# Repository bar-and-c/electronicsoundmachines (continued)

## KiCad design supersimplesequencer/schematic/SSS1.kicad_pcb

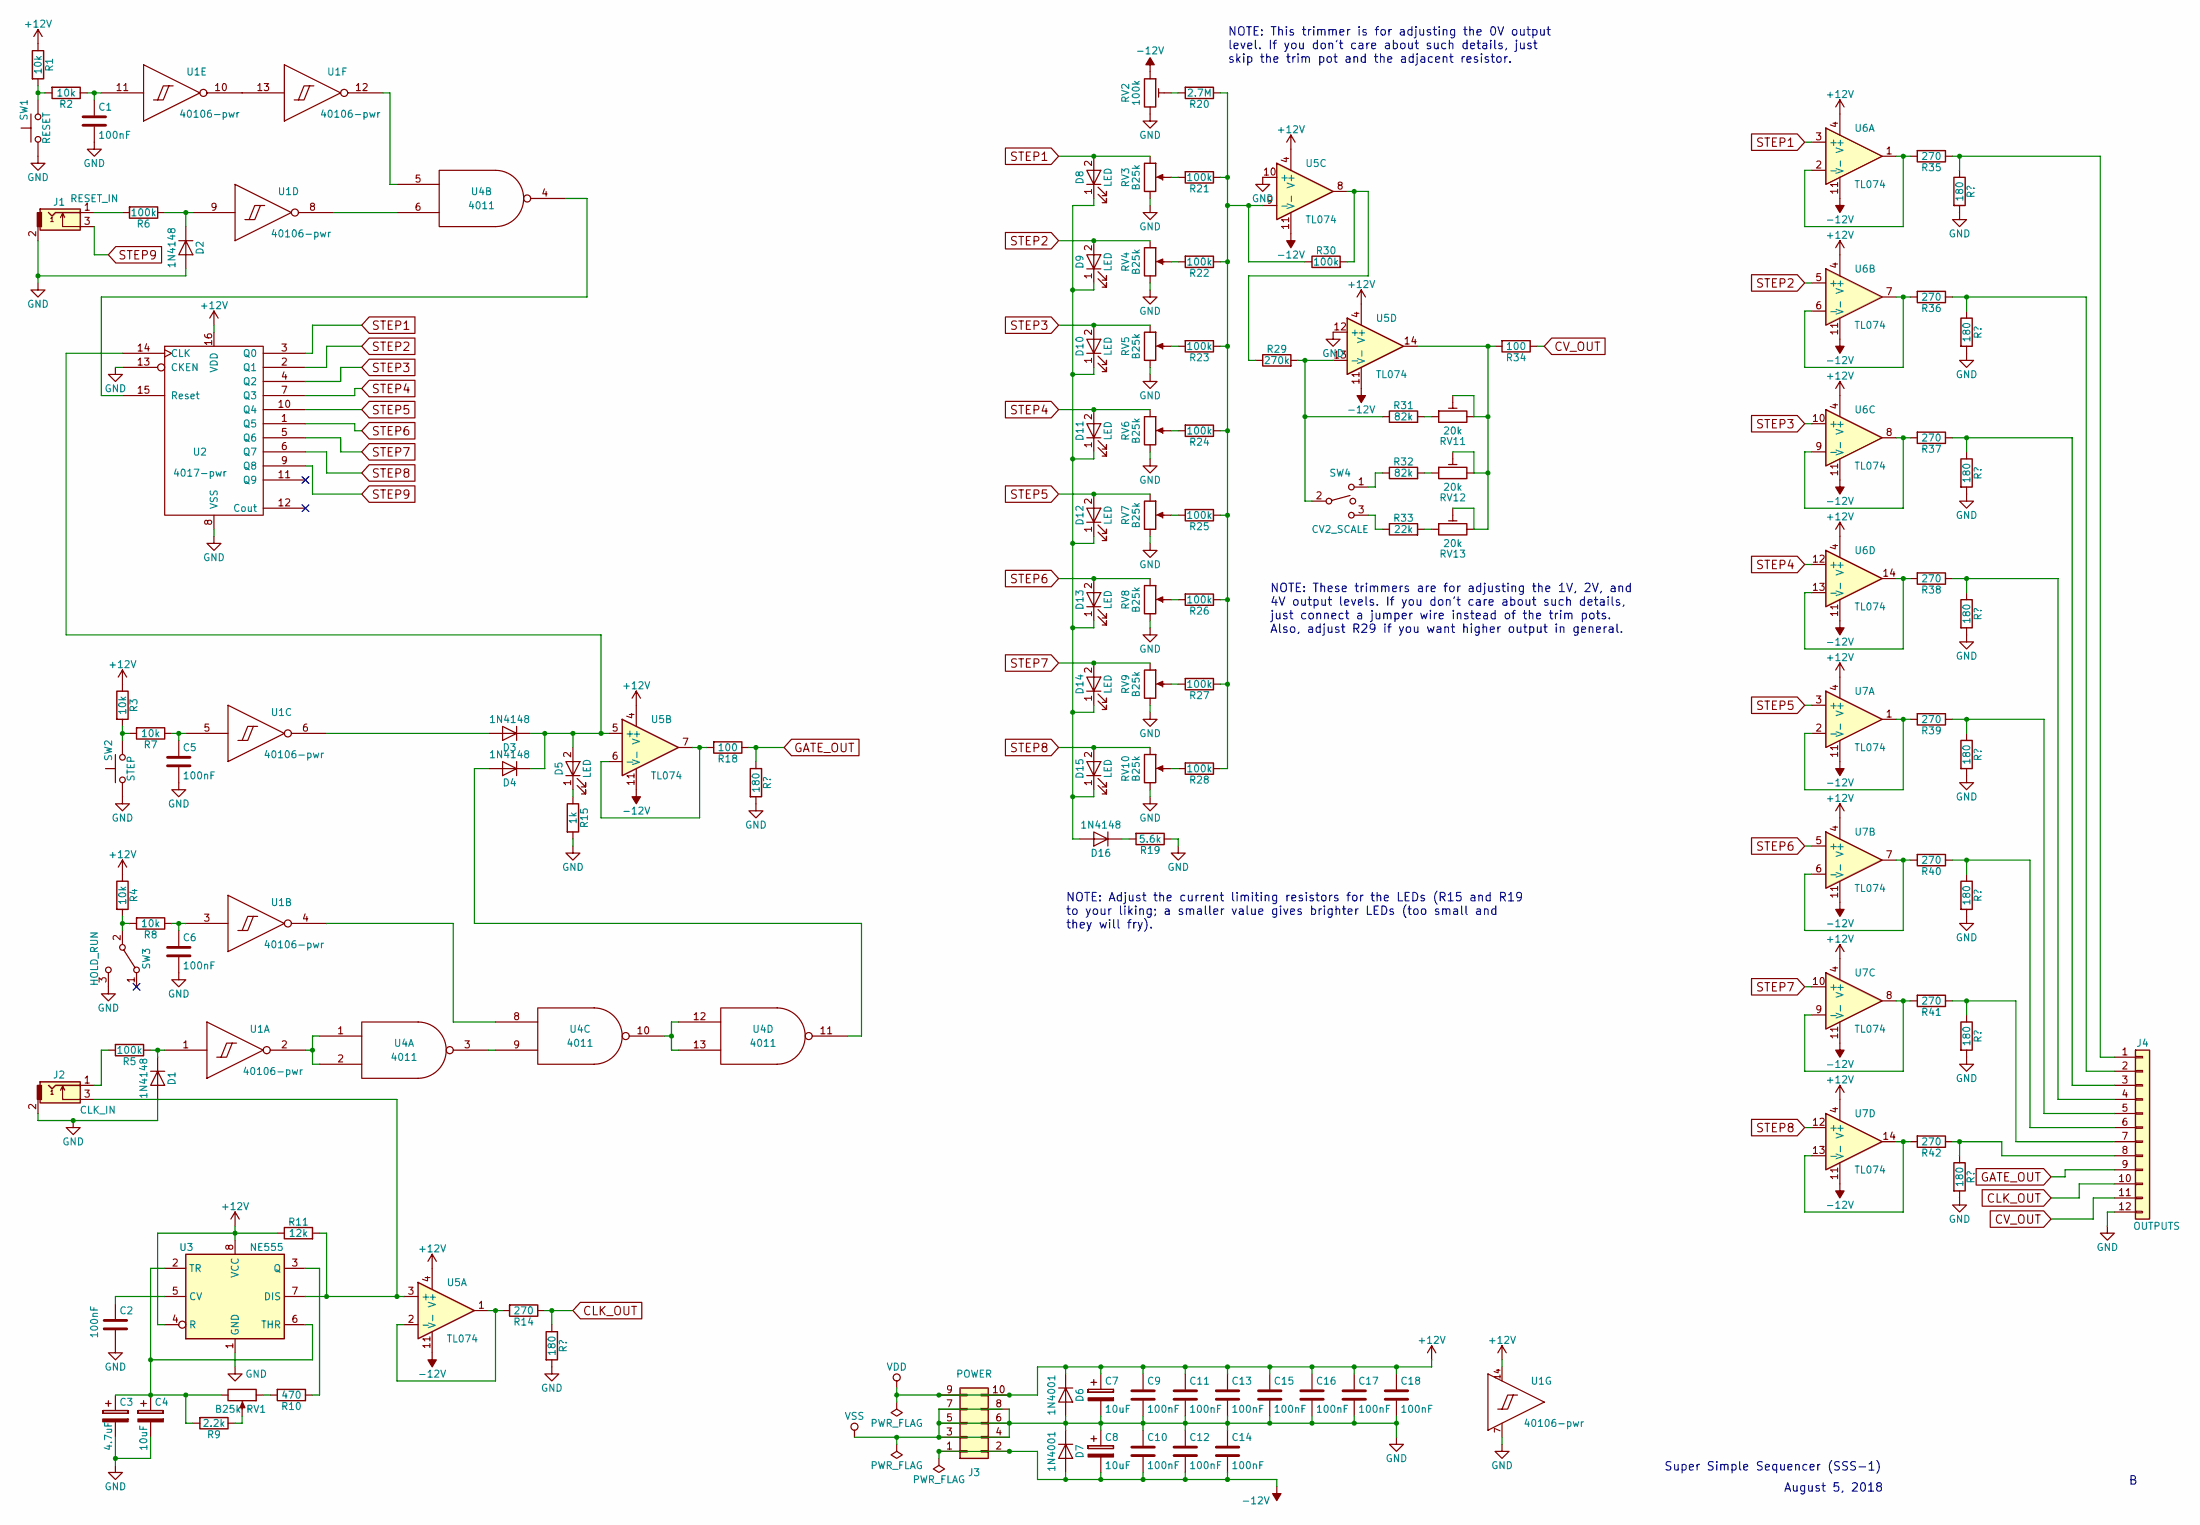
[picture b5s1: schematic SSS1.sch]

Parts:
C1, C2, C5, C6, C9, C10, C11, C12, C13, C14, C15, C16, C17, C18: 100nF; C_Rect_L7.2mm_W3.5mm_P5.00mm_FKS2_FKP2_MKS2_MKP2
C3: 4.7uF; CP_Radial_D5.0mm_P2.00mm
C4, C7, C8: 10uF; CP_Radial_D5.0mm_P2.00mm
D1, D2, D3, D4, D16: 1N4148; D_A-405_P7.62mm_Horizontal
D5, D8, D9, D10, D11, D12, D13, D14, D15: LED; LED_D3.0mm
D6, D7: 1N4001; D_DO-41_SOD81_Horizontal_RM10
J1: RESET_IN; Socket_Strip_Straight_1x03_Pitch2.54mm
J2: CLK_IN; Socket_Strip_Straight_1x03_Pitch2.54mm
J3: POWER; Pin_Header_Straight_2x05_Pitch2.54mm
J4: OUTPUTS; Pin_Header_Straight_1x12_Pitch2.54mm
R1, R2, R3, R4, R7, R8: 10k; R_Axial_DIN0207_L6.3mm_D2.5mm_P7.62mm_Horizontal
R5, R6, R21, R22, R23, R24, R25, R26, R27, R28, R30: 100k; R_Axial_DIN0207_L6.3mm_D2.5mm_P7.62mm_Horizontal
R9: 2.2k; R_Axial_DIN0207_L6.3mm_D2.5mm_P7.62mm_Horizontal
R10: 470; R_Axial_DIN0207_L6.3mm_D2.5mm_P7.62mm_Horizontal
R11: 12k; R_Axial_DIN0207_L6.3mm_D2.5mm_P7.62mm_Horizontal
R14, R35, R36, R37, R38, R39, R40, R41, R42: 270; R_Axial_DIN0207_L6.3mm_D2.5mm_P7.62mm_Horizontal
R15: 1k; R_Axial_DIN0207_L6.3mm_D2.5mm_P7.62mm_Horizontal
R18, R34: 100; R_Axial_DIN0207_L6.3mm_D2.5mm_P7.62mm_Horizontal
R19: 5.6k; R_Axial_DIN0207_L6.3mm_D2.5mm_P7.62mm_Horizontal
R20: 2.7M; R_Axial_DIN0207_L6.3mm_D2.5mm_P7.62mm_Horizontal
R29: 270k; R_Axial_DIN0207_L6.3mm_D2.5mm_P7.62mm_Horizontal
R31, R32: 82k; R_Axial_DIN0207_L6.3mm_D2.5mm_P7.62mm_Horizontal
R33: 22k; R_Axial_DIN0207_L6.3mm_D2.5mm_P7.62mm_Horizontal
RV1, RV3, RV4, RV5, RV6, RV7, RV8, RV9, RV10: B25k; Potentiometer_Alps_RK09Y_Vertical
RV2: 100k; Potentiometer_Trimmer_Vishay_T73XX_Vertical
RV11, RV12, RV13: 20k; Potentiometer_Trimmer_Vishay_T73XX_Vertical
SW1: RESET; Pin_Header_Straight_2x01_Pitch2.54mm
SW2: STEP; Pin_Header_Straight_2x01_Pitch2.54mm
SW3: HOLD_RUN; Pin_Header_Straight_1x03_Pitch2.54mm
SW4: CV2_SCALE; Socket_Strip_Straight_1x03_Pitch2.54mm
U1: 40106-pwr; DIP-14_W7.62mm_Socket_LongPads
U2: 4017-pwr; DIP-16_W7.62mm_Socket_LongPads
U3: NE555; DIP-8_W7.62mm_Socket_LongPads
U4: 4011; DIP-14_W7.62mm_LongPads
U5, U6, U7: TL074; DIP-14_W7.62mm_LongPads

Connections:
+12V: C7.1, C9.1, C11.1, C13.1, C15.1, C16.1, C17.1, C18.1, D6.1 (K), J3.9, J3.10, R1.1, R3.1, R4.1, R11.1, U1.14 (VDD), U2.16 (VDD), U3.4 (R), U3.8 (VCC), U4.14 (VDD), U5.4 (V+), U6.4 (V+), U7.4 (V+)
-12V: C8.2, C10.2, C12.2, C14.2, D7.2 (A), J3.1, J3.2, RV2.1, U5.11 (V-), U6.11 (V-), U7.11 (V-)
CLK_OUT: J4.10, R14.1
CV_OUT: J4.11, R34.1
GATE_OUT: J4.9, R18.1
GND: C1.2, C2.2, C3.2, C4.2, C5.2, C6.2, C7.2, C8.1, C9.2, C10.1, C11.2, C12.1, C13.2, C14.1, C15.2, C16.2, C17.2, C18.2, D1.2 (A), D2.2 (A), D6.2 (A), D7.1 (K), J1.2, J2.2, J3.3, J3.4, J3.5, J3.6, J3.7, J3.8, J4.12, R15.2, R19.1, RV2.3, RV3.3, RV4.3, RV5.3, RV6.3, RV7.3, RV8.3, RV9.3, RV10.3, SW1.1, SW2.1, SW3.3 (C), U1.7 (VSS), U2.8 (VSS), U2.13 (CKEN), U3.1 (GND), U4.7 (VSS), U5.10 (+), U5.12 (+); also elsewhere on the board
unnamed: C1.1, R2.1, U1.11 (In)
unnamed: C2.1, U3.5 (CV)
unnamed: C3.1, C4.1, R9.2, RV1.3, U3.2 (TR), U3.6 (THR)
unnamed: C5.1, R7.1, U1.5 (In)
unnamed: C6.1, R8.1, U1.3 (In)
unnamed: D1.1 (K), R5.1, U1.1 (In)
unnamed: D2.1 (K), R6.1, U1.9 (In)
unnamed: D3.1 (K), D4.1 (K), D5.2 (A), U2.14 (CLK), U5.5 (+)
unnamed: D3.2 (A), U1.6 (Out)
unnamed: D4.2 (A), U4.11
unnamed: D5.1 (K), R15.1
unnamed: D8.1 (K), D9.1 (K), D10.1 (K), D11.1 (K), D12.1 (K), D13.1 (K), D14.1 (K), D15.1 (K), D16.2 (A)
unnamed: D16.1 (K), R19.2
unnamed: J1.1, R6.2
unnamed: J2.1, R5.2
unnamed: J2.3, R11.2, U3.7 (DIS), U5.3 (+)
unnamed: J4.1, R35.1
unnamed: J4.2, R36.1
unnamed: J4.3, R37.1
unnamed: J4.4, R38.1
unnamed: J4.5, R39.1
unnamed: J4.6, R40.1
unnamed: J4.7, R41.1
unnamed: J4.8, R42.1
unnamed: R1.2, R2.2, SW1.2
unnamed: R3.2, R7.2, SW2.2
unnamed: R4.2, R8.2, SW3.2 (B)
unnamed: R9.1, RV1.2
unnamed: R10.1, U3.3 (Q)
unnamed: R10.2, RV1.1
unnamed: R20.1, R21.1, R22.1, R23.1, R24.1, R25.1, R26.1, R27.1, R28.1, R30.1, U5.9 (-)
unnamed: R20.2, RV2.2
unnamed: R21.2, RV3.2
unnamed: R22.2, RV4.2
unnamed: R23.2, RV5.2
unnamed: R24.2, RV6.2
unnamed: R25.2, RV7.2
unnamed: R26.2, RV8.2
unnamed: R27.2, RV9.2
unnamed: R28.2, RV10.2
unnamed: R29.1, R30.2, U5.8
unnamed: R29.2, R31.1, SW4.2, U5.13 (-)
unnamed: R31.2, RV11.1
unnamed: R32.1, SW4.1
unnamed: R32.2, RV12.1
unnamed: R33.1, SW4.3
unnamed: R33.2, RV13.1
unnamed: R34.2, RV11.2, RV11.3, RV12.2, RV12.3, RV13.2, RV13.3, U5.14
unnamed: R35.2, U6.1, U6.2 (-)
unnamed: R36.2, U6.6 (-), U6.7
unnamed: R37.2, U6.8, U6.9 (-)
unnamed: R38.2, U6.13 (-), U6.14
unnamed: R39.2, U7.1, U7.2 (-)
unnamed: R40.2, U7.6 (-), U7.7
unnamed: R41.2, U7.8, U7.9 (-)
unnamed: R42.2, U7.13 (-), U7.14
unnamed: U1.2 (Out), U4.1, U4.2
unnamed: U1.4 (Out), U4.8
unnamed: U1.8 (Out), U4.6
unnamed: U1.10 (Out), U1.13 (In)
unnamed: U1.12 (Out), U4.5
unnamed: U2.15 (Reset), U4.4
unnamed: U4.3, U4.9
unnamed: U4.10, U4.12, U4.13
STEP1: D8.2 (A), RV3.1, U2.3 (Q0), U6.3 (+)
STEP2: D9.2 (A), RV4.1, U2.2 (Q1), U6.5 (+)
STEP3: D10.2 (A), RV5.1, U2.4 (Q2), U6.10 (+)
STEP4: D11.2 (A), RV6.1, U2.7 (Q3), U6.12 (+)
STEP5: D12.2 (A), RV7.1, U2.10 (Q4), U7.3 (+)
STEP6: D13.2 (A), RV8.1, U2.1 (Q5), U7.5 (+)
STEP7: D14.2 (A), RV9.1, U2.5 (Q6), U7.10 (+)
STEP8: D15.2 (A), RV10.1, U2.6 (Q7), U7.12 (+)
STEP9: J1.3, U2.9 (Q8)

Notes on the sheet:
August 5, 2018
Super Simple Sequencer (SSS-1)
NOTE: Adjust the current limiting resistors for the LEDs (R15 and R19 to your liking; a smaller value gives brighter LEDs (too small and they will fry).
NOTE: These trimmers are for adjusting the 1V, 2V, and 4V output levels. If you don't care about such details, just connect a jumper wire instead of the trim pots. Also, adjust R29 if you want higher output in general.
NOTE: This trimmer is for adjusting the 0V output level. If you don't care about such details, just skip the trim pot and the adjacent resistor.

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
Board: 2 copper layers, 104 parts (0 on the bottom side), 83 nets, no tracks yet.

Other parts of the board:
R12, R16: 220k; R_Axial_DIN0207_L6.3mm_D2.5mm_P7.62mm_Horizontal
R13, R17: 100k; R_Axial_DIN0207_L6.3mm_D2.5mm_P7.62mm_Horizontal

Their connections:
GND: R12.1, R16.1; also elsewhere on the board

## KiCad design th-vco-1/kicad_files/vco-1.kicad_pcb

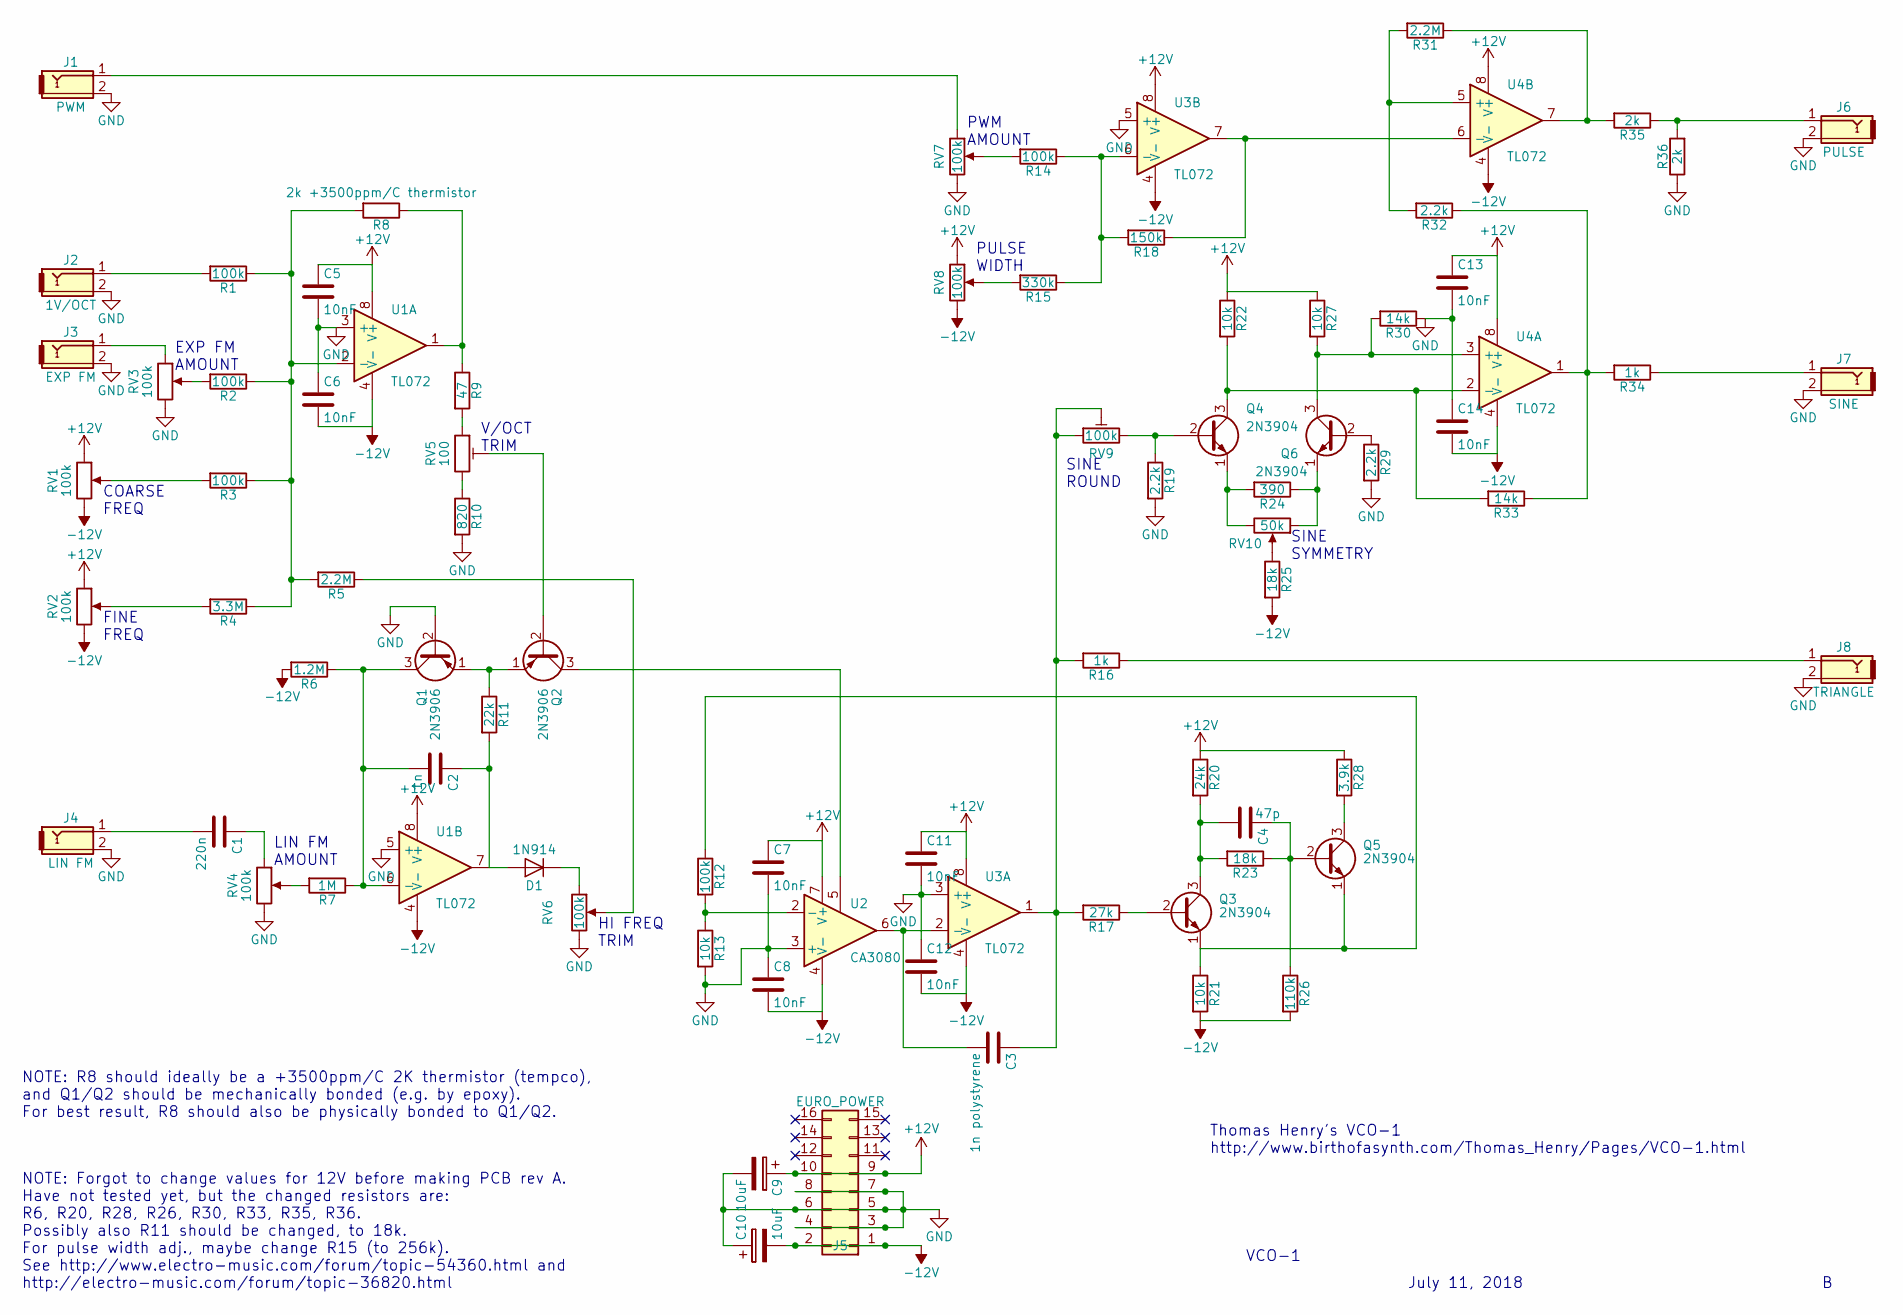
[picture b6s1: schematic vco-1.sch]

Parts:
C1: 220n; C_Rect_L7.2mm_W3.5mm_P5.00mm_FKS2_FKP2_MKS2_MKP2
C2: 1n; C_Rect_L7.2mm_W3.5mm_P5.00mm_FKS2_FKP2_MKS2_MKP2
C3: 1n polystyrene; C_Axial_L3.8mm_D2.6mm_P7.50mm_Horizontal
C4: 47p; C_Rect_L7.2mm_W3.5mm_P5.00mm_FKS2_FKP2_MKS2_MKP2
C5, C6, C7, C8, C11, C12, C13, C14: 10nF; C_Rect_L7.2mm_W3.5mm_P5.00mm_FKS2_FKP2_MKS2_MKP2
C9, C10: 10uF; CP_Radial_D5.0mm_P2.00mm
D1: 1N914; D_DO-35_SOD27_P7.62mm_Horizontal
J1: PWM; Pin_Header_Straight_1x02_Pitch2.54mm
J2: 1V/OCT; Pin_Header_Straight_1x02_Pitch2.54mm
J3: EXP FM; Pin_Header_Straight_1x02_Pitch2.54mm
J4: LIN FM; Pin_Header_Straight_1x02_Pitch2.54mm
J5: EURO_POWER; Pin_Header_Straight_2x08_Pitch2.54mm
J6: PULSE; Pin_Header_Straight_1x02_Pitch2.54mm
J7: SINE; Pin_Header_Straight_1x02_Pitch2.54mm
J8: TRIANGLE; Pin_Header_Straight_1x02_Pitch2.54mm
Q1, Q2: 2N3906; TO-92_Inline_Wide
Q3, Q4, Q5, Q6: 2N3904; TO-92_Inline_Wide
R1, R2, R3, R12, R14: 100k; R_Axial_DIN0207_L6.3mm_D2.5mm_P7.62mm_Horizontal
R4: 3.3M; R_Axial_DIN0207_L6.3mm_D2.5mm_P7.62mm_Horizontal
R5, R31: 2.2M; R_Axial_DIN0207_L6.3mm_D2.5mm_P7.62mm_Horizontal
R6: 1.2M; R_Axial_DIN0207_L6.3mm_D2.5mm_P7.62mm_Horizontal
R7: 1M; R_Axial_DIN0207_L6.3mm_D2.5mm_P7.62mm_Horizontal
R8: 2k +3500ppm/C thermistor; R_Axial_DIN0309_L9.0mm_D3.2mm_P12.70mm_Horizontal
R9: 47; R_Axial_DIN0207_L6.3mm_D2.5mm_P7.62mm_Horizontal
R10: 820; R_Axial_DIN0207_L6.3mm_D2.5mm_P7.62mm_Horizontal
R11: 22k; R_Axial_DIN0207_L6.3mm_D2.5mm_P7.62mm_Horizontal
R13, R21, R22, R27: 10k; R_Axial_DIN0207_L6.3mm_D2.5mm_P7.62mm_Horizontal
R15: 330k; R_Axial_DIN0207_L6.3mm_D2.5mm_P7.62mm_Horizontal
R16, R34: 1k; R_Axial_DIN0207_L6.3mm_D2.5mm_P7.62mm_Horizontal
R17: 27k; R_Axial_DIN0207_L6.3mm_D2.5mm_P7.62mm_Horizontal
R18: 150k; R_Axial_DIN0207_L6.3mm_D2.5mm_P7.62mm_Horizontal
R19, R29, R32: 2.2k; R_Axial_DIN0207_L6.3mm_D2.5mm_P7.62mm_Horizontal
R20: 24k; R_Axial_DIN0207_L6.3mm_D2.5mm_P7.62mm_Horizontal
R23, R25: 18k; R_Axial_DIN0207_L6.3mm_D2.5mm_P7.62mm_Horizontal
R24: 390; R_Axial_DIN0207_L6.3mm_D2.5mm_P7.62mm_Horizontal
R26: 110k; R_Axial_DIN0207_L6.3mm_D2.5mm_P7.62mm_Horizontal
R28: 3.9k; R_Axial_DIN0207_L6.3mm_D2.5mm_P7.62mm_Horizontal
R30, R33: 14k; R_Axial_DIN0207_L6.3mm_D2.5mm_P7.62mm_Horizontal
R35, R36: 2k; R_Axial_DIN0207_L6.3mm_D2.5mm_P7.62mm_Horizontal
RV1, RV2, RV3, RV4, RV7, RV8: 100k; Potentiometer_Alps_RK09Y_Vertical
RV5: 100; Potentiometer_Trimmer_Bourns_3266Y
RV6, RV9: 100k; Potentiometer_Trimmer_ACP_CA6h_Vertical
RV10: 50k; Potentiometer_Trimmer_ACP_CA6h_Vertical
U1, U3, U4: TL072; DIP-8_W7.62mm_Socket_LongPads
U2: CA3080; DIP-8_W7.62mm_Socket_LongPads

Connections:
+12V: C5.1, C7.1, C9.1, C11.1, C13.1, J5.9, J5.10, R20.1, R22.1, R27.1, R28.1, RV1.1, RV2.1, RV8.1, U1.8 (V+), U2.7 (V+), U3.8 (V+), U4.8 (V+)
-12V: C6.2, C8.2, C10.2, C12.2, C14.2, J5.1, J5.2, R6.2, R21.2, R25.2, R26.2, RV1.3, RV2.3, RV8.3, U1.4 (V-), U2.4 (V-), U3.4 (V-), U4.4 (V-)
GND: C5.2, C6.1, C7.2, C8.1, C9.2, C10.1, C11.2, C12.1, C13.2, C14.1, J1.2, J2.2, J3.2, J4.2, J5.3, J5.4, J5.5, J5.6, J5.7, J5.8, J6.2, J7.2, J8.2, Q1.2 (B), R10.2, R13.2, R19.2, R29.2, R30.1, R36.1, RV3.3, RV4.3, RV6.3, RV7.3, U1.3 (+), U1.5 (+), U2.3 (+), U3.3 (+), U3.5 (+)
unnamed: C1.1, RV4.1
unnamed: C1.2, J4.1
unnamed: C2.1, D1.2 (A), R11.2, U1.7
unnamed: C2.2, Q1.3 (C), R6.1, R7.1, U1.6 (-)
unnamed: C3.1, R16.2, R17.2, RV9.1, RV9.2, U3.1
unnamed: C3.2, U2.6, U3.2 (-)
unnamed: C4.1, Q5.2 (B), R23.1, R26.1
unnamed: C4.2, Q3.3 (C), R20.2, R23.2
unnamed: D1.1 (K), RV6.1
unnamed: J1.1, RV7.1
unnamed: J2.1, R1.2
unnamed: J3.1, RV3.1
unnamed: J6.1, R35.1, R36.2
unnamed: J7.1, R34.1
unnamed: J8.1, R16.1
unnamed: Q1.1 (E), Q2.1 (E), R11.1
unnamed: Q2.2 (B), RV5.2
unnamed: Q2.3 (C), U2.5
unnamed: Q3.1 (E), Q5.1 (E), R12.1, R21.1
unnamed: Q3.2 (B), R17.1
unnamed: Q4.1 (E), R24.2, RV10.3
unnamed: Q4.2 (B), R19.1, RV9.3
unnamed: Q4.3 (C), R22.2, R33.2, U4.2 (-)
unnamed: Q5.3 (C), R28.2
unnamed: Q6.1 (E), R24.1, RV10.1
unnamed: Q6.2 (B), R29.1
unnamed: Q6.3 (C), R27.2, R30.2, U4.3 (+)
unnamed: R1.1, R2.1, R3.1, R4.1, R5.2, R8.2, U1.2 (-)
unnamed: R2.2, RV3.2
unnamed: R3.2, RV1.2
unnamed: R4.2, RV2.2
unnamed: R5.1, RV6.2
unnamed: R7.2, RV4.2
unnamed: R8.1, R9.1, U1.1
unnamed: R9.2, RV5.1
unnamed: R10.1, RV5.3
unnamed: R12.2, R13.1, U2.2 (-)
unnamed: R14.1, R15.1, R18.2, U3.6 (-)
unnamed: R14.2, RV7.2
unnamed: R15.2, RV8.2
unnamed: R18.1, U3.7, U4.6 (-)
unnamed: R25.1, RV10.2
unnamed: R31.1, R35.2, U4.7
unnamed: R31.2, R32.2, U4.5 (+)
unnamed: R32.1, R33.1, R34.2, U4.1

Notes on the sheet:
Thomas Henry's VCO-1 http://www.birthofasynth.com/Thomas_Henry/Pages/VCO-1.html
VCO-1
July 11, 2018
HI FREQ TRIM
LIN FM AMOUNT
V/OCT TRIM
EXP FM AMOUNT
COARSE FREQ
FINE FREQ
SINE SYMMETRY
SINE ROUND
PWM AMOUNT
PULSE WIDTH
NOTE: R8 should ideally be a +3500ppm/C 2K thermistor (tempco), and Q1/Q2 should be mechanically bonded (e.g. by epoxy). For best result, R8 should also be physically bonded to Q1/Q2.
NOTE: Forgot to change values for 12V before making PCB rev A. Have not tested yet, but the changed resistors are: R6, R20, R28, R26, R30, R33, R35, R36. Possibly also R11 should be changed, to 18k. For pulse width adj., maybe change R15 (to 256k). See http://www.electro-music.com/forum/topic-54360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

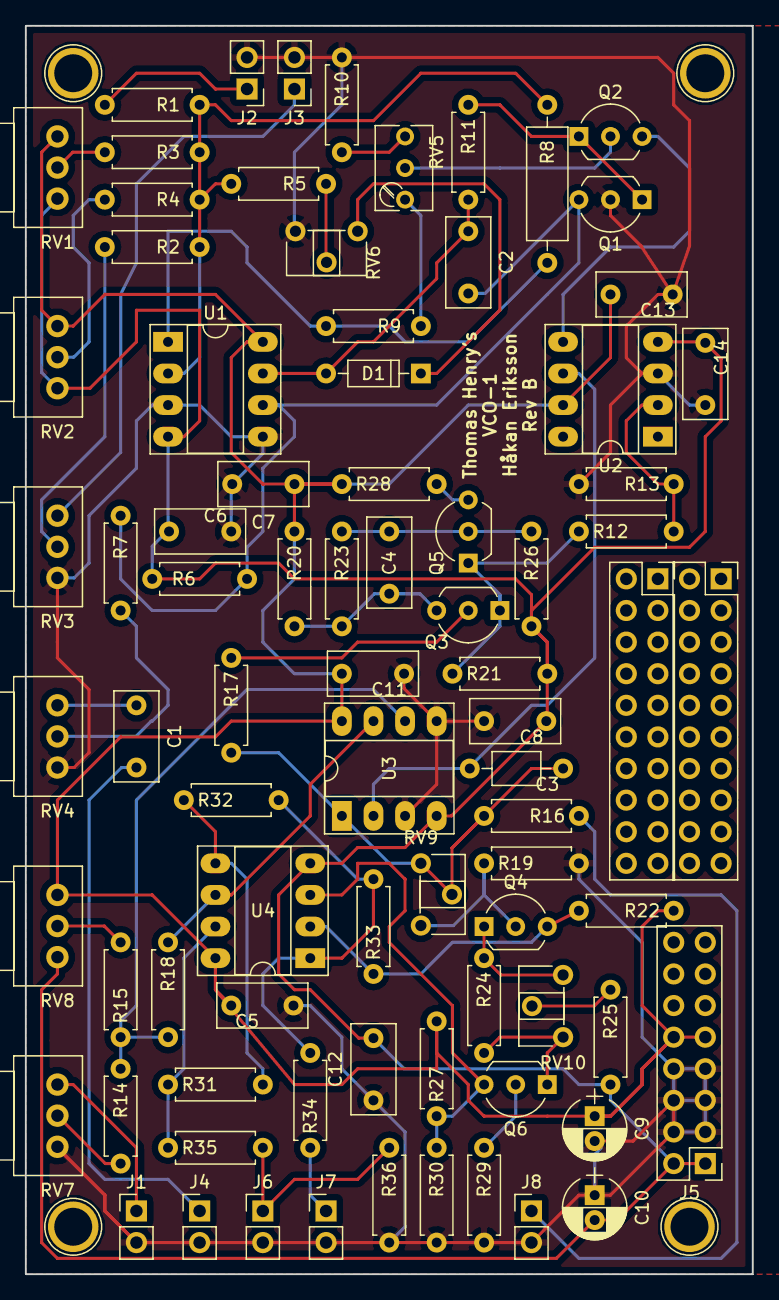
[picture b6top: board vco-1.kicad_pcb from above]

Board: 2 copper layers, 58.4 x 100.3 mm, 79 parts (0 on the bottom side), 48 nets.
